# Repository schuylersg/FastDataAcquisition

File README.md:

FastDataAcquisition
===================

A high speed (1 GSPS+) data acquisition circuit. This project is currently in development. All schematics and boards are not finalized.

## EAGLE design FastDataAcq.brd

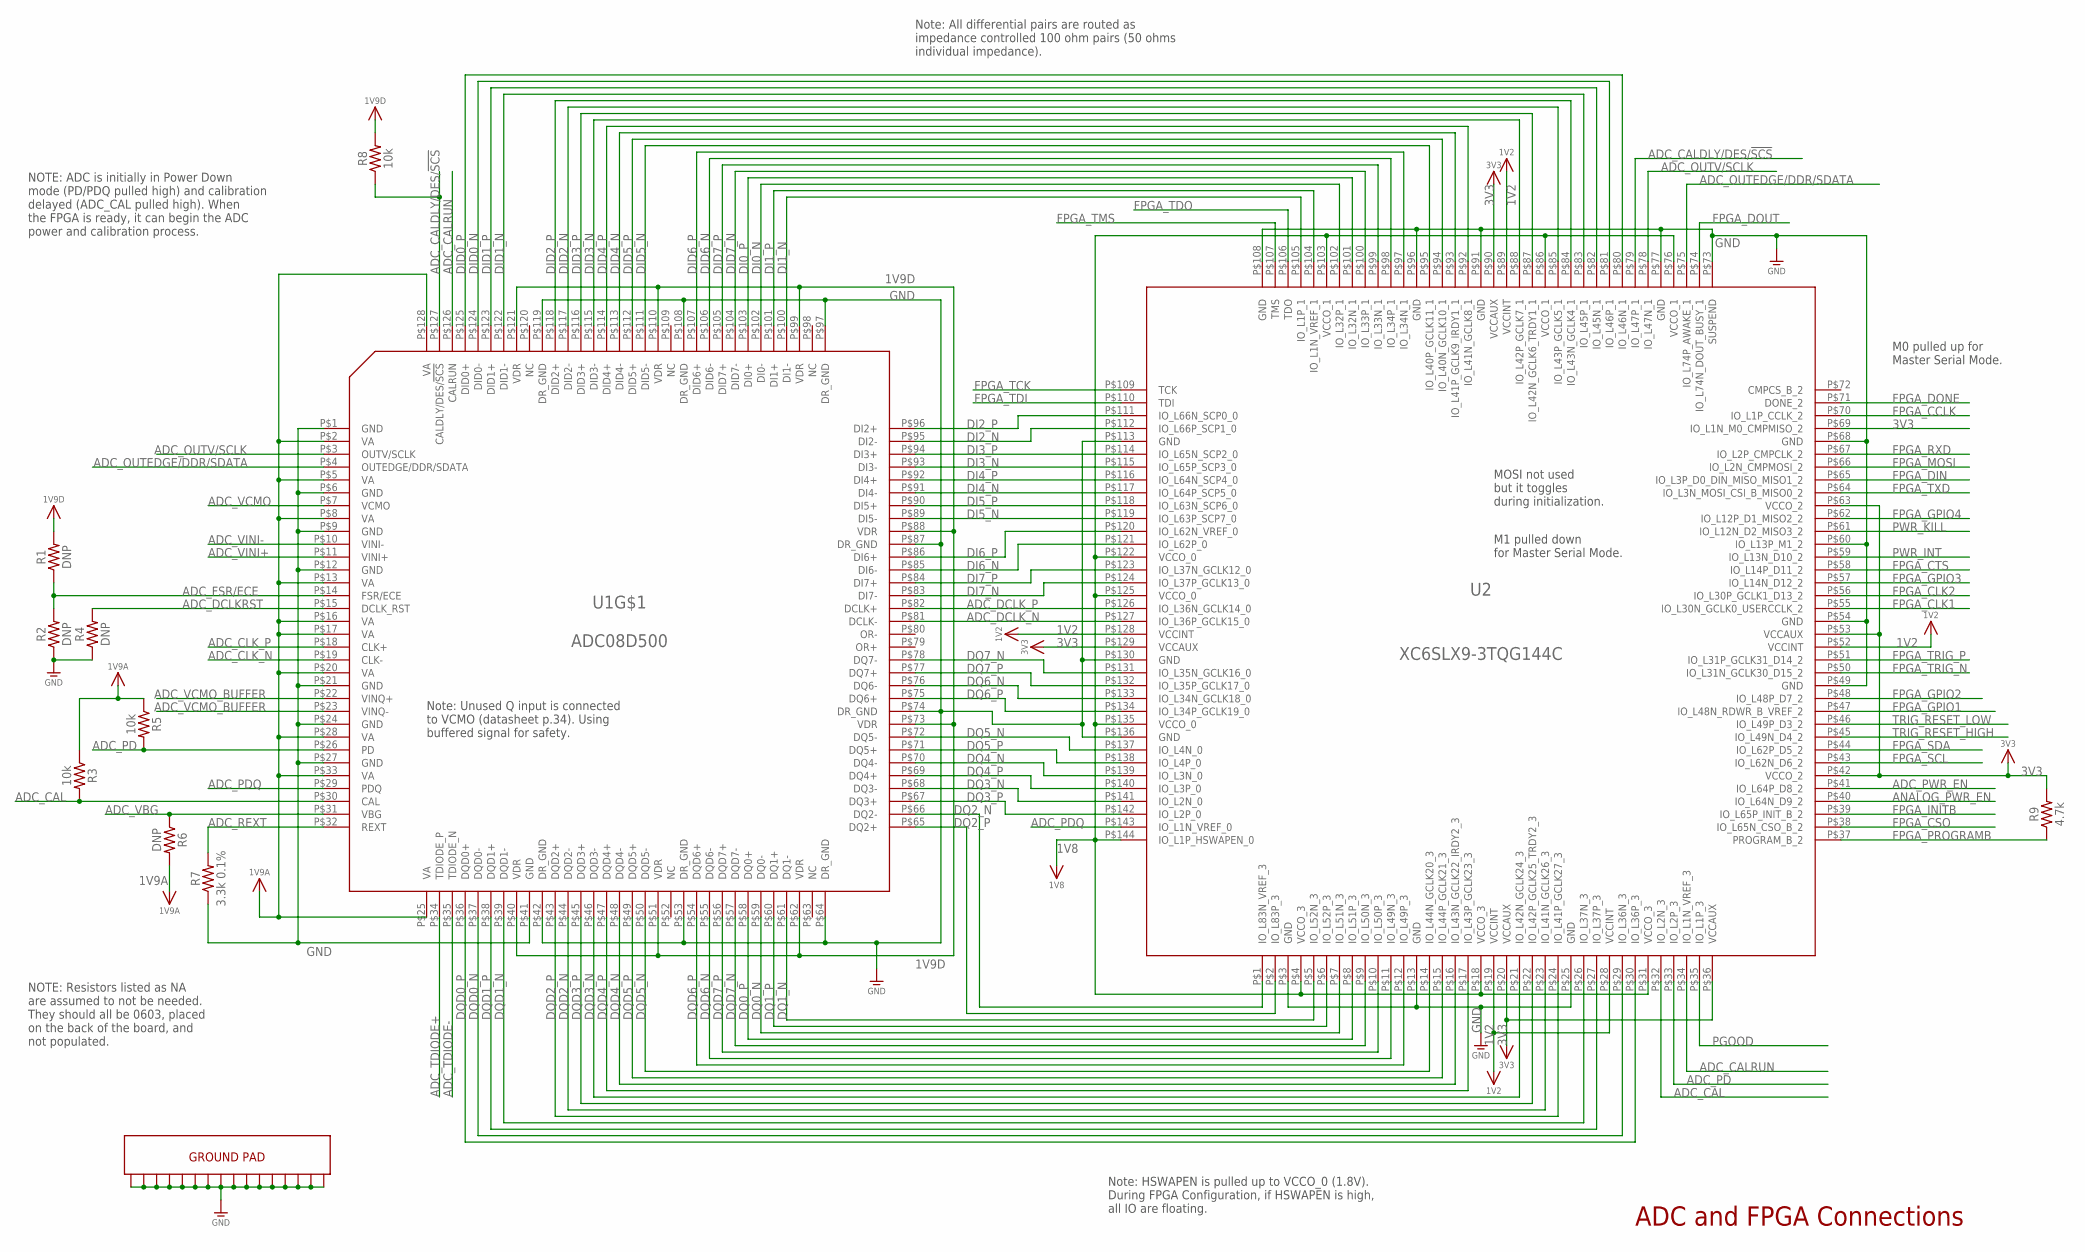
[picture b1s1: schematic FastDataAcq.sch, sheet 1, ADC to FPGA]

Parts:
R1, R2, R4, R6: DNP; R0603
R3, R5, R8: 10k; R0201; MANPARTNUMBER RC0603J103CS
R7: 3.3k 0.1%; R0603; PARTNUMBER P3.3KDBCT-ND
R9: 4.7k; R0201; MANPARTNUMBER ERJ-1GNJ472C
U1: ADC08D500; 128HLQFP; PARTNUMBER ADC08D500CIYB/NOPB-ND
U2: XC6SLX9-3TQG144C; TQG144

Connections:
1V2: U2.P$19 (VCCINT), U2.P$28 (VCCINT), U2.P$52 (VCCINT), U2.P$89 (VCCINT), U2.P$128 (VCCINT); also elsewhere on the board
1V8: U2.P$4 (VCCO_3), U2.P$18 (VCCO_3), U2.P$31 (VCCO_3), U2.P$76 (VCCO_1), U2.P$86 (VCCO_1), U2.P$103 (VCCO_1), U2.P$122 (VCCO_0), U2.P$125 (VCCO_0), U2.P$135 (VCCO_0), U2.P$144 (IO_L1P_HSWAPEN_0); also elsewhere on the board
1V9A: R3.1, R5.1, R6.2, U1.P$2 (VA), U1.P$5 (VA), U1.P$8 (VA), U1.P$13 (VA), U1.P$16 (VA), U1.P$17 (VA), U1.P$20 (VA), U1.P$25 (VA), U1.P$28 (VA), U1.P$33 (VA), U1.P$128 (VA); also elsewhere on the board
1V9D: R1.2, R8.2, U1.P$40 (VDR), U1.P$51 (VDR), U1.P$62 (VDR), U1.P$73 (VDR), U1.P$88 (VDR), U1.P$99 (VDR), U1.P$110 (VDR), U1.P$121 (VDR); also elsewhere on the board
3V3: R9.2, U2.P$20 (VCCAUX), U2.P$36 (VCCAUX), U2.P$42 (VCCO_2), U2.P$53 (VCCAUX), U2.P$63 (VCCO_2), U2.P$69 (IO_L1N_M0_CMPMISO_2), U2.P$90 (VCCAUX), U2.P$129 (VCCAUX); also elsewhere on the board
ADC_CAL: R3.2, U1.P$30 (CAL), U2.P$32 (IO_L2N_3)
ADC_CALDLY/DES/!SCS: R8.1, U1.P$127 (CALDLY/DES/!SCS), U2.P$79 (IO_L47P_1)
ADC_CALRUN: U1.P$126 (CALRUN), U2.P$34 (IO_L1N_VREF_3)
ADC_CLK_N: U1.P$19 (CLK-); also elsewhere on the board
ADC_CLK_P: U1.P$18 (CLK+); also elsewhere on the board
ADC_DCLKRST: R4.2, U1.P$15 (DCLK_RST)
ADC_DCLK_N: U1.P$81 (DCLK-), U2.P$127 (IO_L36P_GCLK15_0)
ADC_DCLK_P: U1.P$82 (DCLK+), U2.P$126 (IO_L36N_GCLK14_0)
ADC_FSR/ECE: R1.1, R2.2, U1.P$14 (FSR/ECE)
ADC_OUTEDGE/DDR/SDATA: U1.P$4 (OUTEDGE/DDR/SDATA), U2.P$75 (IO_L74P_AWAKE_1)
ADC_OUTV/SCLK: U1.P$3 (OUTV/SCLK), U2.P$78 (IO_L47N_1)
ADC_PD: R5.2, U1.P$26 (PD), U2.P$33 (IO_L2P_3)
ADC_PDQ: U1.P$29 (PDQ), U2.P$143 (IO_L1N_VREF_0)
ADC_PWR_EN: U2.P$41 (IO_L64P_D8_2); also elsewhere on the board
ADC_REXT: R7.2, U1.P$32 (REXT)
ADC_TDIODE+: U1.P$34 (TDIODE_P); also elsewhere on the board
ADC_TDIODE-: U1.P$35 (TDIODE_N); also elsewhere on the board
ADC_VBG: R6.1, U1.P$31 (VBG)
ADC_VCMO: U1.P$7 (VCMO); also elsewhere on the board
ADC_VCMO_BUFFER: U1.P$22 (VINQ+), U1.P$23 (VINQ-); also elsewhere on the board
ADC_VINI+: U1.P$11 (VINI+); also elsewhere on the board
ADC_VINI-: U1.P$10 (VINI-); also elsewhere on the board
ANALOG_PWR_EN: U2.P$40 (IO_L64N_D9_2); also elsewhere on the board
DI0_N: U1.P$102 (DI0-), U2.P$102 (IO_L32P_1)
DI0_P: U1.P$103 (DI0+), U2.P$101 (IO_L32N_1)
DI1_N: U1.P$100 (DI1-), U2.P$105 (IO_L1P_1)
DI1_P: U1.P$101 (DI1+), U2.P$104 (IO_L1N_VREF_1)
DI2_N: U1.P$95 (DI2-), U2.P$112 (IO_L66P_SCP1_0)
DI2_P: U1.P$96 (DI2+), U2.P$111 (IO_L66N_SCP0_0)
DI3_N: U1.P$93 (DI3-), U2.P$115 (IO_L65P_SCP3_0)
DI3_P: U1.P$94 (DI3+), U2.P$114 (IO_L65N_SCP2_0)
DI4_N: U1.P$91 (DI4-), U2.P$117 (IO_L64P_SCP5_0)
DI4_P: U1.P$92 (DI4+), U2.P$116 (IO_L64N_SCP4_0)
DI5_N: U1.P$89 (DI5-), U2.P$119 (IO_L63P_SCP7_0)
DI5_P: U1.P$90 (DI5+), U2.P$118 (IO_L63N_SCP6_0)
DI6_N: U1.P$85 (DI6-), U2.P$121 (IO_L62P_0)
DI6_P: U1.P$86 (DI6+), U2.P$120 (IO_L62N_VREF_0)
DI7_N: U1.P$83 (DI7-), U2.P$124 (IO_L37P_GCLK13_0)
DI7_P: U1.P$84 (DI7+), U2.P$123 (IO_L37N_GCLK12_0)
DID0_N: U1.P$124 (DID0-), U2.P$81 (IO_L46P_1)
DID0_P: U1.P$125 (DID0+), U2.P$80 (IO_L46N_1)
DID1_N: U1.P$122 (DID1-), U2.P$83 (IO_L45P_1)
DID1_P: U1.P$123 (DID1+), U2.P$82 (IO_L45N_1)
DID2_N: U1.P$117 (DID2-), U2.P$85 (IO_L43P_GCLK5_1)
DID2_P: U1.P$118 (DID2+), U2.P$84 (IO_L43N_GCLK4_1)
DID3_N: U1.P$115 (DID3-), U2.P$88 (IO_L42P_GCLK7_1)
DID3_P: U1.P$116 (DID3+), U2.P$87 (IO_L42N_GCLK6_TRDY1_1)
DID4_N: U1.P$113 (DID4-), U2.P$93 (IO_L41P_GCLK9_IRDY1_1)
DID4_P: U1.P$114 (DID4+), U2.P$92 (IO_L41N_GCLK8_1)
DID5_N: U1.P$111 (DID5-), U2.P$95 (IO_L40P_GCLK11_1)
DID5_P: U1.P$112 (DID5+), U2.P$94 (IO_L40N_GCLK10_1)
DID6_N: U1.P$106 (DID6-), U2.P$98 (IO_L34P_1)
DID6_P: U1.P$107 (DID6+), U2.P$97 (IO_L34N_1)
DID7_N: U1.P$104 (DID7-), U2.P$100 (IO_L33P_1)
DID7_P: U1.P$105 (DID7+), U2.P$99 (IO_L33N_1)
DQ0_N: U1.P$59 (DQ0-), U2.P$7 (IO_L51N_3)
DQ0_P: U1.P$58 (DQ0+), U2.P$8 (IO_L51P_3)
DQ1_N: U1.P$61 (DQ1-), U2.P$5 (IO_L52N_3)
DQ1_P: U1.P$60 (DQ1+), U2.P$6 (IO_L52P_3)
DQ2_N: U1.P$66 (DQ2-), U2.P$1 (IO_L83N_VREF_3)
DQ2_P: U1.P$65 (DQ2+), U2.P$2 (IO_L83P_3)
DQ3_N: U1.P$68 (DQ3-), U2.P$141 (IO_L2N_0)
DQ3_P: U1.P$67 (DQ3+), U2.P$142 (IO_L2P_0)
DQ4_N: U1.P$70 (DQ4-), U2.P$139 (IO_L3N_0)
DQ4_P: U1.P$69 (DQ4+), U2.P$140 (IO_L3P_0)
DQ5_N: U1.P$72 (DQ5-), U2.P$137 (IO_L4N_0)
DQ5_P: U1.P$71 (DQ5+), U2.P$138 (IO_L4P_0)
DQ6_N: U1.P$76 (DQ6-), U2.P$133 (IO_L34N_GCLK18_0)
DQ6_P: U1.P$75 (DQ6+), U2.P$134 (IO_L34P_GCLK19_0)
DQ7_N: U1.P$78 (DQ7-), U2.P$131 (IO_L35N_GCLK16_0)
DQ7_P: U1.P$77 (DQ7+), U2.P$132 (IO_L35P_GCLK17_0)
DQD0_N: U1.P$37 (DQD0-), U2.P$29 (IO_L36N_3)
DQD0_P: U1.P$36 (DQD0+), U2.P$30 (IO_L36P_3)
DQD1_N: U1.P$39 (DQD1-), U2.P$26 (IO_L37N_3)
DQD1_P: U1.P$38 (DQD1+), U2.P$27 (IO_L37P_3)
DQD2_N: U1.P$44 (DQD2-), U2.P$23 (IO_L41N_GCLK26_3)
DQD2_P: U1.P$43 (DQD2+), U2.P$24 (IO_L41P_GCLK27_3)
DQD3_N: U1.P$46 (DQD3-), U2.P$21 (IO_L42N_GCLK24_3)
DQD3_P: U1.P$45 (DQD3+), U2.P$22 (IO_L42P_GCLK25_TRDY2_3)
DQD4_N: U1.P$48 (DQD4-), U2.P$16 (IO_L43N_GCLK22_IRDY2_3)
DQD4_P: U1.P$47 (DQD4+), U2.P$17 (IO_L43P_GCLK23_3)
DQD5_N: U1.P$50 (DQD5-), U2.P$14 (IO_L44N_GCLK20_3)
DQD5_P: U1.P$49 (DQD5+), U2.P$15 (IO_L44P_GCLK21_3)
DQD6_N: U1.P$55 (DQD6-), U2.P$11 (IO_L49N_3)
DQD6_P: U1.P$54 (DQD6+), U2.P$12 (IO_L49P_3)
DQD7_N: U1.P$57 (DQD7-), U2.P$9 (IO_L50N_3)
DQD7_P: U1.P$56 (DQD7+), U2.P$10 (IO_L50P_3)
FPGA_CCLK: U2.P$70 (IO_L1P_CCLK_2); also elsewhere on the board
FPGA_CLK1: U2.P$55 (IO_L30N_GCLK0_USERCCLK_2); also elsewhere on the board
FPGA_CLK2: U2.P$56 (IO_L30P_GCLK1_D13_2); also elsewhere on the board
FPGA_CSO: U2.P$38 (IO_L65N_CSO_B_2)
FPGA_CTS: U2.P$58 (IO_L14P_D11_2); also elsewhere on the board
FPGA_DIN: U2.P$65 (IO_L3P_D0_DIN_MISO_MISO1_2); also elsewhere on the board
FPGA_DONE: U2.P$71 (DONE_2); also elsewhere on the board
FPGA_DOUT: U2.P$74 (IO_L74N_DOUT_BUSY_1)
FPGA_GPIO1: U2.P$47 (IO_L48N_RDWR_B_VREF_2); also elsewhere on the board
FPGA_GPIO2: U2.P$48 (IO_L48P_D7_2); also elsewhere on the board
FPGA_GPIO3: U2.P$57 (IO_L14N_D12_2); also elsewhere on the board
FPGA_GPIO4: U2.P$62 (IO_L12P_D1_MISO2_2); also elsewhere on the board
FPGA_INITB: U2.P$39 (IO_L65P_INIT_B_2); also elsewhere on the board
FPGA_MOSI: U2.P$66 (IO_L2N_CMPMOSI_2)
FPGA_PROGRAMB: R9.1, U2.P$37 (PROGRAM_B_2); also elsewhere on the board
FPGA_RXD: U2.P$67 (IO_L2P_CMPCLK_2); also elsewhere on the board
FPGA_SCL: U2.P$43 (IO_L62N_D6_2); also elsewhere on the board
FPGA_SDA: U2.P$44 (IO_L62P_D5_2); also elsewhere on the board
FPGA_TCK: U2.P$109 (TCK); also elsewhere on the board
FPGA_TDI: U2.P$110 (TDI); also elsewhere on the board
FPGA_TDO: U2.P$106 (TDO); also elsewhere on the board
FPGA_TMS: U2.P$107 (TMS); also elsewhere on the board
FPGA_TRIG_N: U2.P$50 (IO_L31N_GCLK30_D15_2); also elsewhere on the board
FPGA_TRIG_P: U2.P$51 (IO_L31P_GCLK31_D14_2); also elsewhere on the board
FPGA_TXD: U2.P$64 (IO_L3N_MOSI_CSI_B_MISO0_2); also elsewhere on the board
GND: R2.1, R4.1, R7.1, U1.P$1 (GND), U1.P$6 (GND), U1.P$9 (GND), U1.P$12 (GND), U1.P$21 (GND), U1.P$24 (GND), U1.P$27 (GND), U1.P$41 (GND), U1.P$42 (DR_GND), U1.P$53 (DR_GND), U1.P$64 (DR_GND), U1.P$74 (DR_GND), U1.P$87 (DR_GND), U1.P$97 (DR_GND), U1.P$108 (DR_GND), U1.P$119 (DR_GND), U1.P$129 (GND), U1.P$130 (GND), U1.P$131 (GND), U1.P$132 (GND), U1.P$133 (GND), U1.P$134 (GND), U1.P$135 (GND), U1.P$136 (GND), U1.P$137 (GND), U1.P$138 (GND), U1.P$139 (GND), U1.P$140 (GND), U1.P$141 (GND), U1.P$142 (GND), U1.P$143 (GND), U1.P$144 (GND), U2.P$3 (GND), U2.P$13 (GND), U2.P$25 (GND), U2.P$49 (GND), U2.P$54 (GND), U2.P$60 (IO_L13P_M1_2), U2.P$68 (GND), U2.P$73 (SUSPEND), U2.P$77 (GND), U2.P$91 (GND), U2.P$96 (GND), U2.P$108 (GND), U2.P$113 (GND), U2.P$130 (GND), U2.P$136 (GND); also elsewhere on the board
PGOOD: U2.P$35 (IO_L1P_3); also elsewhere on the board
PWR_INT: U2.P$59 (IO_L13N_D10_2); also elsewhere on the board
PWR_KILL: U2.P$61 (IO_L12N_D2_MISO3_2); also elsewhere on the board
TRIG_RESET_HIGH: U2.P$45 (IO_L49N_D4_2); also elsewhere on the board
TRIG_RESET_LOW: U2.P$46 (IO_L49P_D3_2); also elsewhere on the board

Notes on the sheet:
ADC and FPGA Connections
Note: Unused Q input is connected to VCMO (datasheet p.34). Using buffered signal for safety.
MOSI not used but it toggles during initialization.
M0 pulled up for Master Serial Mode.
M1 pulled down for Master Serial Mode.
Note: HSWAPEN is pulled up to VCCO_0 (1.8V). During FPGA Configuration, if HSWAPEN is high, all IO are floating.
NOTE: Resistors listed as NA are assumed to not be needed. They should all be 0603, placed on the back of the board, and not populated.
NOTE: ADC is initially in Power Down mode (PD/PDQ pulled high) and calibration delayed (ADC_CAL pulled high). When the FPGA is ready, it can begin the ADC power and calibration process.
Note: All differential pairs are routed as impedance controlled 100 ohm pairs (50 ohms individual impedance).

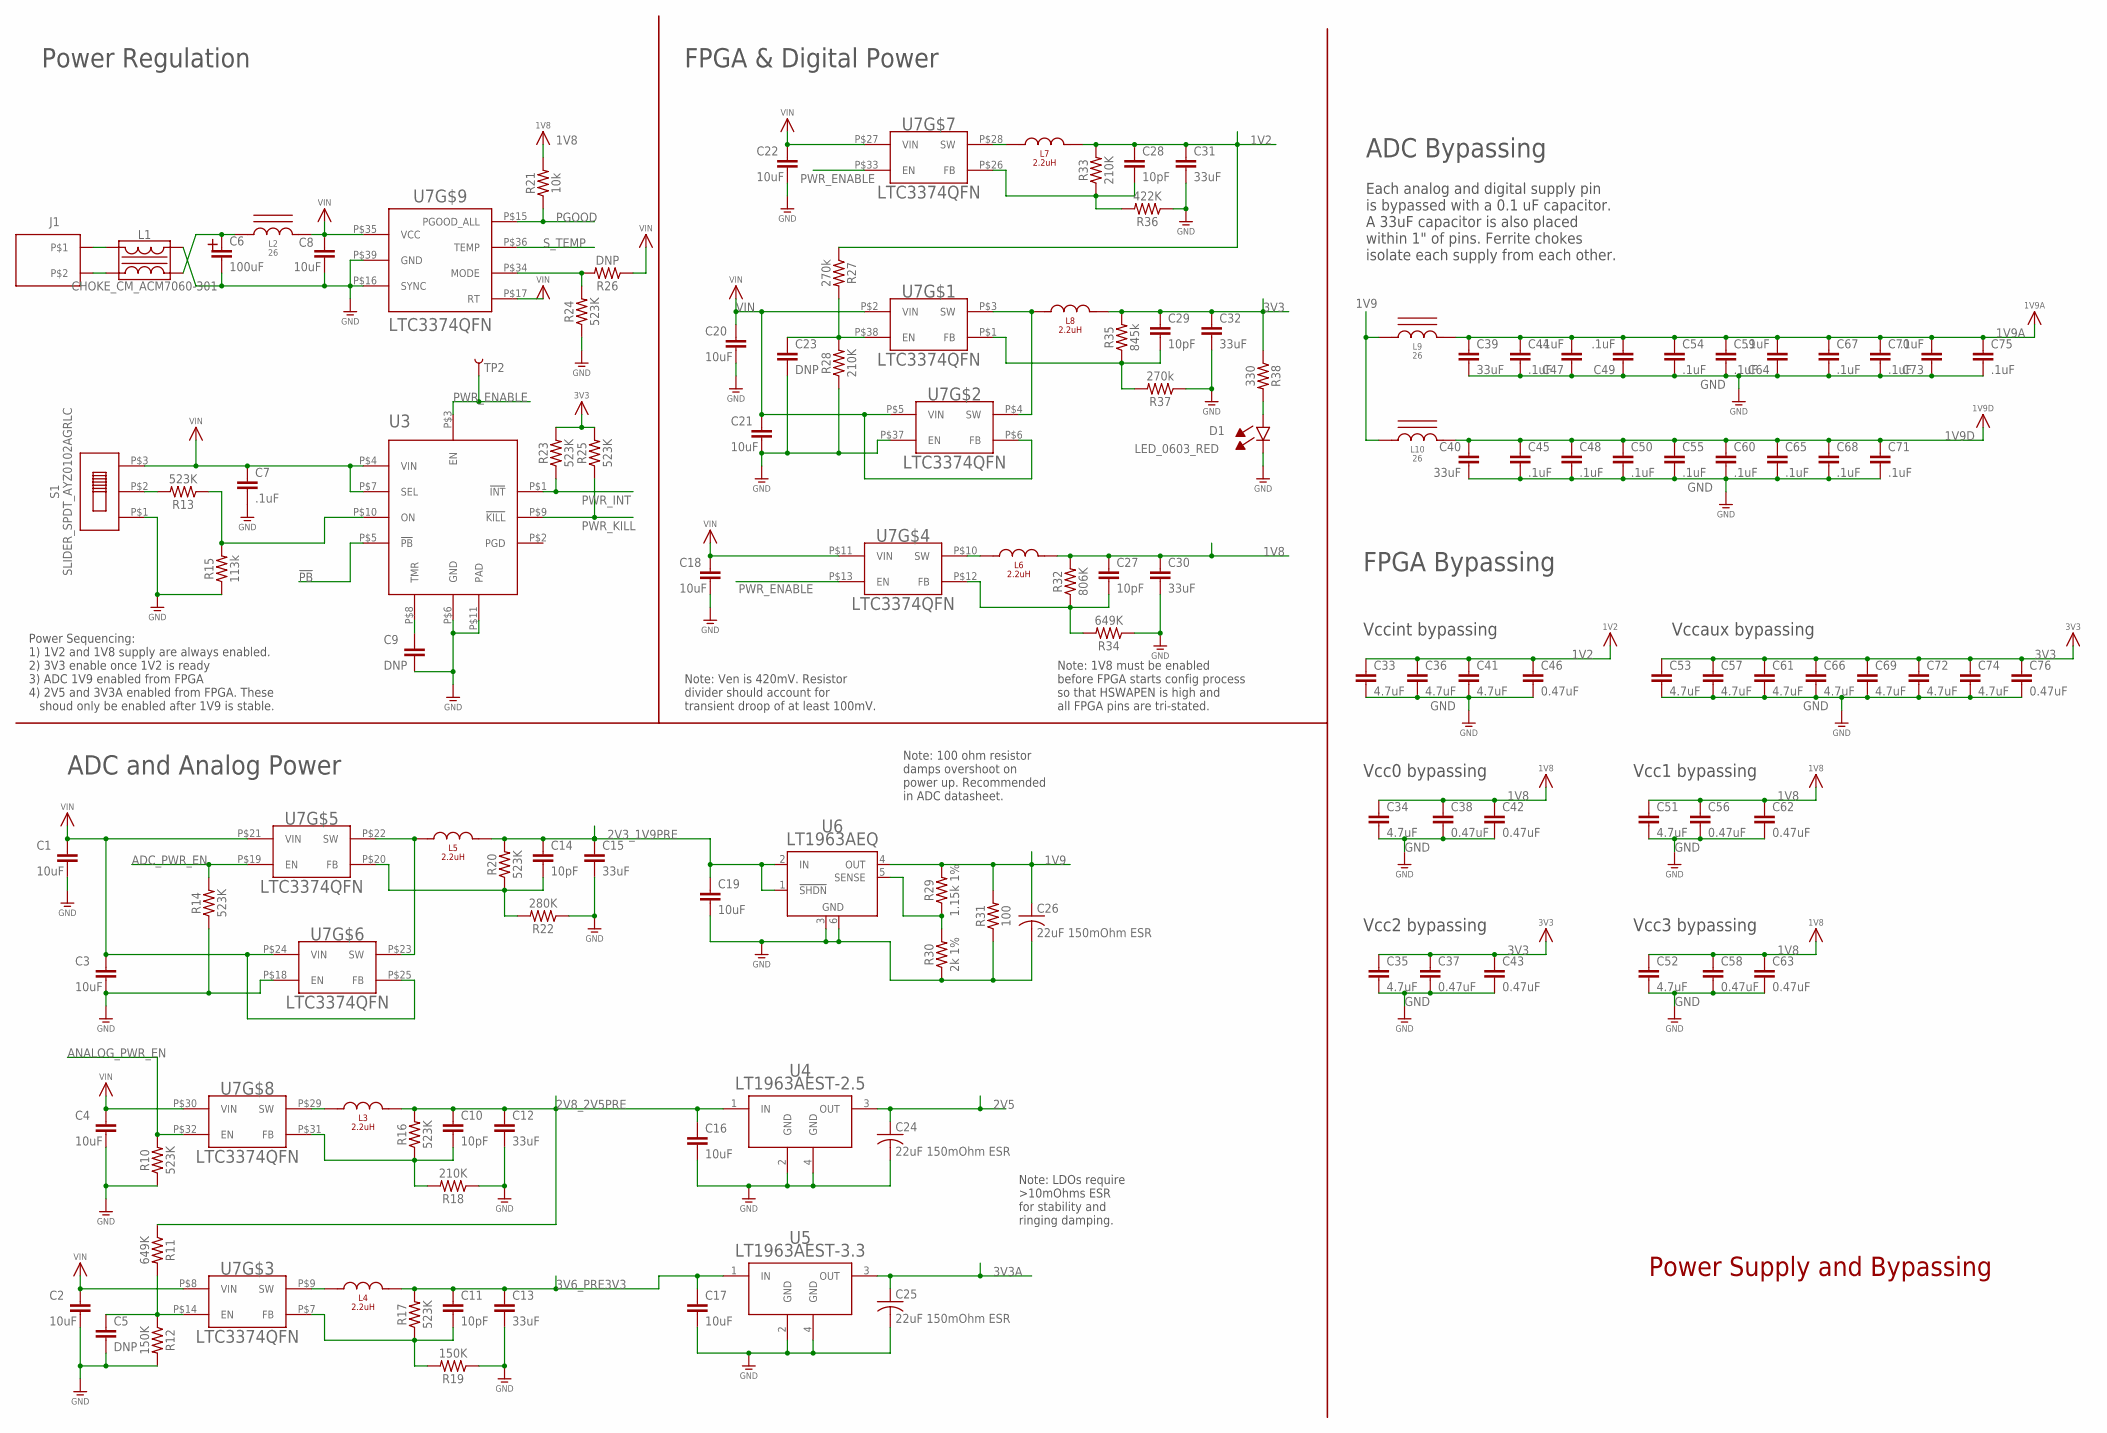
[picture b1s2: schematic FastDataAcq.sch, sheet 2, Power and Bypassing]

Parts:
C1, C2, C3, C4, C8, C16, C17, C18, C19, C20, C21, C22: 10uF; C0603; PARTNUMBER 445-4112-1-ND
C5, C9, C23: DNP; C0603
C6: 100uF; 2917_MURATA_CAP; MANPARTNUMBER ECASD91B107M012K00
C7, C44, C45, C47, C48, C49, C50, C54, C55, C59, C60, C64, C65, C67, C68, C70, C71, C73, C75: .1uF; 0204REVERSE; PARTNUMBER 587-2152-1-ND
C10, C11, C14, C27, C28, C29: 10pF; C0201; PARTNUMBER 445-1769-1-ND
C12, C13, C15, C30, C31, C32, C39, C40: 33uF; 0805; PARTNUMBER 445-8238-1-ND
C24, C25, C26: 22uF 150mOhm ESR; C0805; PARTNUMBER P16231CT-ND
C33, C34, C35, C36, C41, C51, C52, C53, C57, C61, C66, C69, C72, C74: 4.7uF; 0402_C; MANPARTNUMBER CL05A475MQ5NRNC
C37, C38, C42, C43, C46, C56, C58, C62, C63, C76: 0.47uF; 0204REVERSE; PARTNUMBER 1276-1779-1-ND
D1: LED_0603_RED; 0603_LED; PARTNUMBER LNJ237W82RACT-ND
J1: MICRO-FIT_3.0_2POS_RA_SMD; MICRO-FIT_3.02POS_RA_SMD
L1: CHOKE_CM_ACM7060-301; ACM7060_CHOKE
L2, L9, L10: 26; MURATA_BLM18
L3, L4, L6, L7: 2.2uH; 3.0X3.6_VISHAY; PARTNUMBER 541-1322-1-ND
L5, L8: 2.2uH; 5.18X5.49_VISHAY; PARTNUMBER 541-1220-1-ND
R10, R13, R14, R16, R17, R20, R23, R24, R25: 523K; R0201; PARTNUMBER P523KABCT-ND
R11, R34: 649K; R0201; PARTNUMBER P649KABCT-ND
R12, R19: 150K; R0201; PARTNUMBER 1276-3719-1-ND
R15: 113k; R0201; PARTNUMBER P113KABCT-ND
R18, R28, R33: 210K; R0201; PARTNUMBER P210KABCT-ND
R21: 10k; R0201; MANPARTNUMBER RC0603J103CS
R22: 280K; R0201; PARTNUMBER P280KABCT-ND
R26: DNP; R0603
R27, R37: 270k; R0201; PARTNUMBER P270KABCT-ND
R29: 1.15k 1%; R0603; MANPARTNUMBER RC1608F1151CS
R30: 2k 1%; R0603; MANPARTNUMBER RC1608F202CS
R31: 100; R0603; MANPARTNUMBER RC1608J101CS
R32: 806K; R0201; PARTNUMBER P806KABCT-ND
R35: 845k; R0201; PARTNUMBER P845KABCT-ND
R36: 422K; R0201; PARTNUMBER P422KABCT-ND
R38: 330; R0201; MANPARTNUMBER RC0603J331CS
S1: SLIDER_SPDT_AYZ0102AGRLC; AYZ0102AGRLC
TP2: TEST-POINT3; PAD.03X.03
U3: LTC2955-1; 10-DFN
U4: LT1963AEST-2.5; SOT223
U5: LT1963AEST-3.3; SOT223
U6: LT1963AEQ; Q5-DD; MANPARTNUMBER LT1963AEQ#PBF
U7: LTC3374QFN; 38-QFN_(5X7)

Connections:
1V2: C28.1, C31.1, C33.P$1 (1), C36.P$1 (1), C41.P$1 (1), C46.P$1 (1), L7.P$2, R27.1, R33.2; also elsewhere on the board
1V8: C27.1, C30.1, C34.P$1 (1), C38.P$1 (1), C42.P$1 (1), C51.P$1 (1), C52.P$1 (1), C56.P$1 (1), C58.P$1 (1), C62.P$1 (1), C63.P$1 (1), L6.P$2, R21.2, R32.2; also elsewhere on the board
1V9: C26.1, L9.P$1, L10.P$1, R29.2, R31.2, U6.4 (OUT)
1V9A: C39.1, C44.P$1 (1), C47.P$2 (2), C49.P$2 (2), C54.P$1 (1), C59.P$1 (1), C64.P$2 (2), C67.P$1 (1), C70.P$1 (1), C73.P$2 (2), C75.P$1 (1), L9.P$2; also elsewhere on the board
1V9D: C40.1, C45.P$1 (1), C48.P$1 (1), C50.P$1 (1), C55.P$1 (1), C60.P$1 (1), C65.P$1 (1), C68.P$1 (1), C71.P$1 (1), L10.P$2; also elsewhere on the board
2V3_1V9PRE: C14.1, C15.1, C19.1, L5.P$2, R20.2, U6.1 (!SHDN), U6.2 (IN)
2V5: C24.1, U4.3 (OUT); also elsewhere on the board
2V8_2V5PRE: C10.1, C12.1, C16.1, L3.P$2, R11.1, R16.2, U4.1 (IN)
3V3: C29.1, C32.1, C35.P$1 (1), C37.P$1 (1), C43.P$1 (1), C53.P$1 (1), C57.P$1 (1), C61.P$1 (1), C66.P$1 (1), C69.P$1 (1), C72.P$1 (1), C74.P$1 (1), C76.P$1 (1), L8.P$2, R23.2, R25.2, R35.2, R38.1; also elsewhere on the board
3V3A: C25.1, U5.3 (OUT); also elsewhere on the board
3V6_PRE3V3: C11.1, C13.1, C17.1, L4.P$2, R17.2, U5.1 (IN)
!PB: U3.P$5 (!PB); also elsewhere on the board
ADC_PWR_EN: R14.2, U7.P$19 (EN); also elsewhere on the board
ANALOG_PWR_EN: R10.2, U7.P$32 (EN); also elsewhere on the board
GND: C1.2, C2.2, C3.2, C4.2, C5.2, C6.P$2 (NEG), C7.P$2 (2), C8.2, C9.2, C12.2, C13.2, C15.2, C16.2, C17.2, C18.2, C19.2, C20.2, C21.2, C22.2, C23.2, C24.2, C25.2, C26.2, C30.2, C31.2, C32.2, C33.P$2 (2), C34.P$2 (2), C35.P$2 (2), C36.P$2 (2), C37.P$2 (2), C38.P$2 (2), C39.2, C40.2, C41.P$2 (2), C42.P$2 (2), C43.P$2 (2), C44.P$2 (2), C45.P$2 (2), C46.P$2 (2), C47.P$1 (1), C48.P$2 (2), C49.P$1 (1), C50.P$2 (2), C51.P$2 (2), C52.P$2 (2), C53.P$2 (2), C54.P$2 (2), C55.P$2 (2), C56.P$2 (2), C57.P$2 (2), C58.P$2 (2), C59.P$2 (2), C60.P$2 (2), C61.P$2 (2), C62.P$2 (2), C63.P$2 (2), C64.P$1 (1), C65.P$2 (2), C66.P$2 (2), C67.P$2 (2), C68.P$2 (2), C69.P$2 (2), C70.P$2 (2), C71.P$2 (2), C72.P$2 (2), C73.P$1 (1), C74.P$2 (2), C75.P$2 (2), C76.P$2 (2), D1.CATHODE, L1.P$4, R10.1, R12.2, R14.1, R15.1, R18.1, R19.1, R22.1, R24.1, R28.1, R30.1, R31.1, R34.1, R36.1, R37.1, S1.P$1, U3.P$6 (GND), U3.P$11 (PAD), U4.2 (GND), U4.4 (GND), U5.2 (GND), U5.4 (GND), U6.3 (GND), U6.6 (GND), U7.P$16 (SYNC), U7.P$18 (EN), U7.P$37 (EN), U7.P$39 (GND); also elsewhere on the board
unnamed: D1.ANODE, R38.2
unnamed: R13.2, S1.P$2
unnamed: R13.1, R15.2, U3.P$10 (ON)
unnamed: R29.1, R30.2, U6.5 (SENSE)
unnamed: C9.1, U3.P$8 (TMR)
unnamed: C6.P$1 (POS), L1.P$3, L2.P$1
unnamed: J1.P$1, L1.P$1
unnamed: J1.P$2, L1.P$2
PGOOD: R21.1, U7.P$15 (PGOOD_ALL); also elsewhere on the board
PWR_ENABLE: TP2.P$1, U3.P$3 (EN), U7.P$13 (EN), U7.P$33 (EN)
PWR_INT: R23.1, U3.P$1 (!INT); also elsewhere on the board
PWR_KILL: R25.1, U3.P$9 (!KILL); also elsewhere on the board
S1EN: C23.1, R27.2, R28.2, U7.P$38 (EN)
S1FB: C29.2, R35.1, R37.2, U7.P$1 (FB)
S1SW: L8.P$1, U7.P$3 (SW), U7.P$4 (SW)
S3EN: C5.1, R11.2, R12.1, U7.P$14 (EN)
S3FB: C11.2, R17.1, R19.2, U7.P$7 (FB)
S3SW: L4.P$1, U7.P$9 (SW)
S4FB: C27.2, R32.1, R34.2, U7.P$12 (FB)
S4SW: L6.P$1, U7.P$10 (SW)
S5FB: C14.2, R20.1, R22.2, U7.P$20 (FB)
S5SW: L5.P$1, U7.P$22 (SW), U7.P$23 (SW)
S7FB: C28.2, R33.1, R36.2, U7.P$26 (FB)
S7SW: L7.P$1, U7.P$28 (SW)
S8FB: C10.2, R16.1, R18.2, U7.P$31 (FB)
S8SW: L3.P$1, U7.P$29 (SW)
S_MODE: R24.2, R26.2, U7.P$34 (MODE)
S_TEMP: U7.P$36 (TEMP); also elsewhere on the board
VIN: C1.1, C2.1, C3.1, C4.1, C7.P$1 (1), C8.1, C18.1, C20.1, C21.1, C22.1, L2.P$2, R26.1, S1.P$3, U3.P$4 (VIN), U3.P$7 (SEL), U7.P$2 (VIN), U7.P$5 (VIN), U7.P$6 (FB), U7.P$8 (VIN), U7.P$11 (VIN), U7.P$17 (RT), U7.P$21 (VIN), U7.P$24 (VIN), U7.P$25 (FB), U7.P$27 (VIN), U7.P$30 (VIN), U7.P$35 (VCC)

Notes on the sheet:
Power Supply and Bypassing
ADC Bypassing
Each analog and digital supply pin is bypassed with a 0.1 uF capacitor. A 33uF capacitor is also placed within 1" of pins. Ferrite chokes isolate each supply from each other.
FPGA Bypassing
Vccint bypassing
Vccaux bypassing
Vcc0 bypassing
Vcc1 bypassing
Vcc2 bypassing
Vcc3 bypassing
Note: Ven is 420mV. Resistor divider should account for transient droop of at least 100mV.
Power Regulation
FPGA & Digital Power
ADC and Analog Power
Note: LDOs require >10mOhms ESR for stability and ringing damping.
Power Sequencing: 1) 1V2 and 1V8 supply are always enabled. 2) 3V3 enable once 1V2 is ready 3) ADC 1V9 enabled from FPGA 4) 2V5 and 3V3A enabled from FPGA. These shoud only be enabled after 1V9 is stable.
Note: 100 ohm resistor damps overshoot on power up. Recommended in ADC datasheet.
Note: 1V8 must be enabled before FPGA starts config process so that HSWAPEN is high and all FPGA pins are tri-stated.

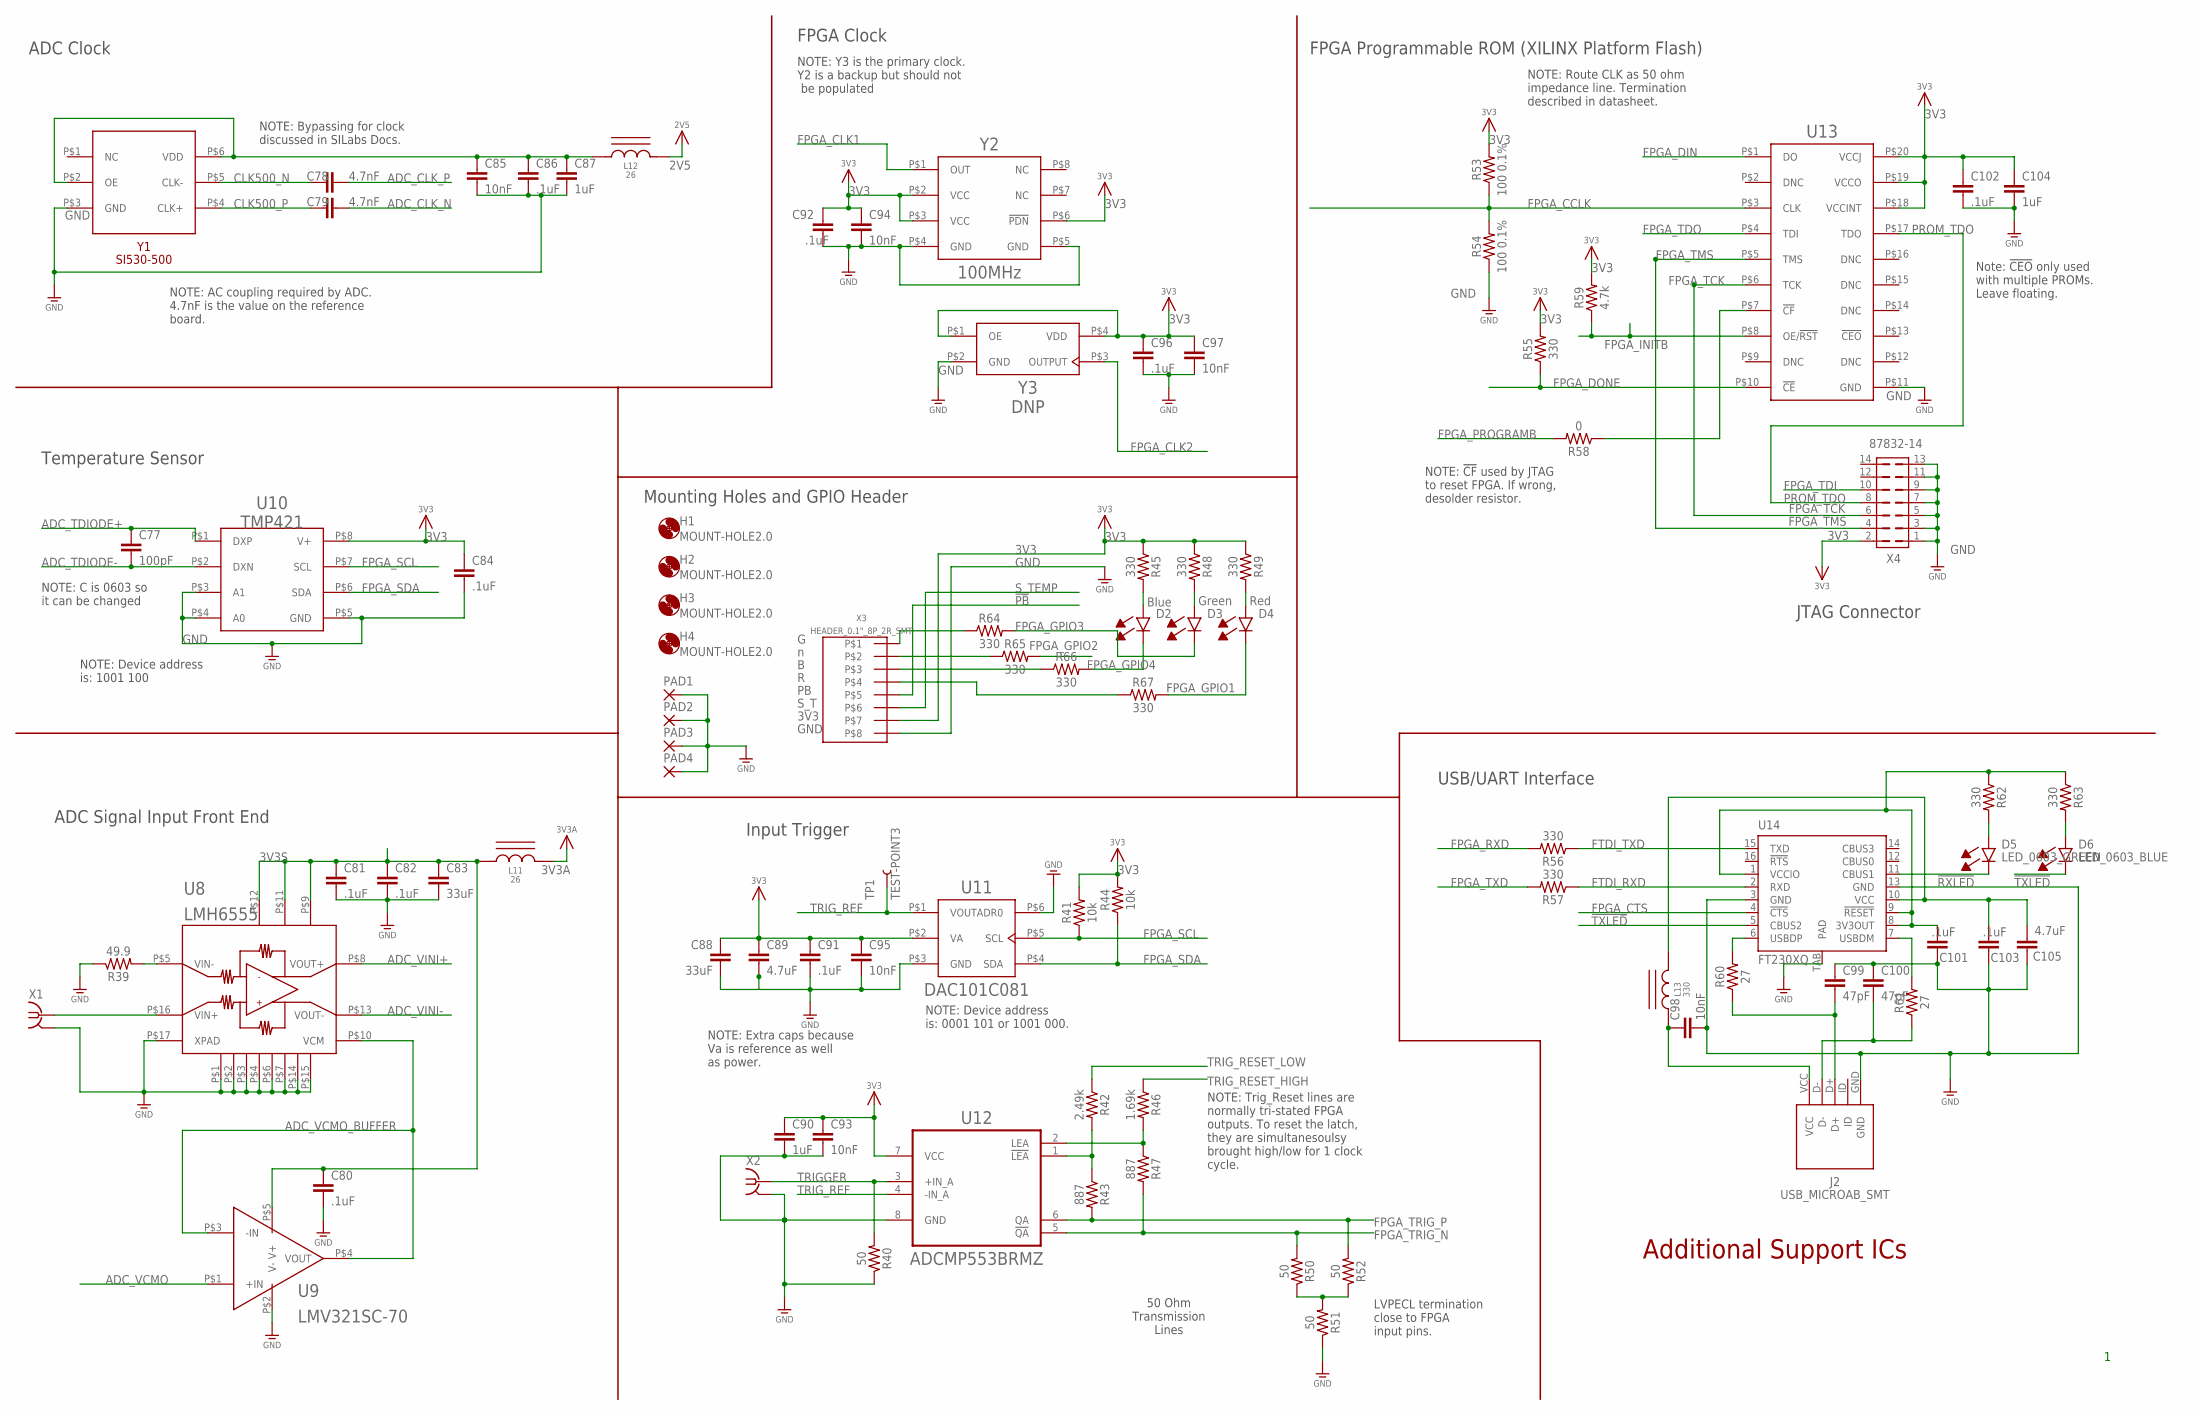
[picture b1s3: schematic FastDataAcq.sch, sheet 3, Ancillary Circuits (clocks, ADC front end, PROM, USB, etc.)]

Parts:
C77: 100pF; C0201; PARTNUMBER 445-4675-1-ND
C78, C79: 4.7nF; C0201; PARTNUMBER 445-13726-1-ND
C80, C81, C82, C84, C86, C91, C92, C96, C101, C102, C103: .1uF; 0204REVERSE; PARTNUMBER 587-2152-1-ND
C83, C88: 33uF; 0805; PARTNUMBER 445-8238-1-ND
C85, C93, C94, C95, C97, C98: 10nF; C0201; PARTNUMBER 445-1793-1-ND
C87, C90, C104: 1uF; 0204REVERSE; PARTNUMBER 445-9091-1-ND
C89, C105: 4.7uF; 0402_C; MANPARTNUMBER CL05A475MQ5NRNC
C99, C100: 47pF; C0201; PARTNUMBER 445-1782-1-ND
D2, D6: LED_0603_BLUE; 0603_LED
D3, D5: LED_0603_GREEN; 0603_LED
D4: LED_0603_RED; 0603_LED; PARTNUMBER LNJ237W82RACT-ND
H1, H2, H3, H4: MOUNT-HOLE2.0; 2.0
J2: USB_MICROAB_SMT; USB_MICROAB_SMT_1
L11, L12: 26; MURATA_BLM18
L13: 330; MURATA_BLM18
PAD1, PAD2, PAD3, PAD4: SMD2; SMD1,27-2,54
R39: 49.9; R0201; MANPARTNUMBER RC0603F49R9C
R40, R50, R51, R52: 50; R0201; MANPARTNUMBER RC0603F49R9C
R41, R44: 10k; R0201; MANPARTNUMBER RC0603J103CS
R42: 2.49k; R0603; PARTNUMBER 1276-4681-1-ND
R43, R47: 887; R0201; MANPARTNUMBER ERJ-1GEF8870C
R45, R48, R49, R55, R56, R57, R62, R63, R64, R65, R66, R67: 330; R0201; MANPARTNUMBER RC0603J331CS
R46: 1.69k; R0603; PARTNUMBER 1276-3491-1-ND
R53, R54: 100 0.1%; R0402; MANPARTNUMBER ERA-3AEB101V
R58: 0; R0603; PARTNUMBER 311-0.0GRCT-ND
R59: 4.7k; R0201; MANPARTNUMBER ERJ-1GNJ472C
R60, R61: 27; R0201; PARTNUMBER 1276-3577-1-ND
TP1: TEST-POINT3; PAD.03X.03
U8: LMH6555; 16WQFN
U9: LMV321SC-70; SC-70
U10: TMP421; SOT23-8
U11: DAC101C081; SOT23-6
U12: ADCMP553BRMZ; SOP65P490X110-8N
U13: XCFXXS04; TSSOP20_XILINX
U14: FT230XQ; QFN16
X1, X2: SMA-142-0701-801/806; J502-ND-142-0701-801/806; MANPARTNUMBER 142-0701-801
X3: HEADER_0.1"_8P_2R_SMT; HEADER_8P_2R_SMT
X4: 87832-14
Y1: SI530-500; SI530
Y2: 100MHz; UMAX8
Y3: DNP; SI500S

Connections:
2V5: L12.P$2; also elsewhere on the board
2V5A: C85.1, C86.P$1 (1), C87.P$1 (1), L12.P$1, Y1.P$2 (OE), Y1.P$6 (VDD)
3V3: C84.P$1 (1), C88.1, C89.P$1 (1), C90.P$1 (1), C91.P$1 (1), C92.P$1 (1), C93.1, C94.1, C95.1, C96.P$1 (1), C97.1, C102.P$1 (1), C104.P$1 (1), R41.2, R44.2, R45.1, R48.1, R49.1, R53.2, R55.2, R59.2, U10.P$8 (V+), U11.P$2 (VA), U12.7 (VCC), U13.P$18 (VCCINT), U13.P$19 (VCCO), U13.P$20 (VCCJ), X3.P$7, X4.2, Y2.P$2 (VCC), Y2.P$3 (VCC), Y2.P$6 (!PDN), Y3.P$1 (OE), Y3.P$4 (VDD); also elsewhere on the board
3V3A: L11.P$2; also elsewhere on the board
3V3OUT: C101.P$2 (2), R62.1, R63.1, U14.1 (VCCIO), U14.8 (3V3OUT), U14.9 (!RESET)
3V3S: C80.P$1 (1), C81.P$1 (1), C82.P$1 (1), C83.1, L11.P$1, U8.P$9 (VCC), U8.P$11 (VCC), U8.P$12 (VCC), U9.P$5 (V+)
5VUSB: C103.P$2 (2), C105.P$2 (2), L13.P$2, U14.10 (VCC)
5VUSB_CON: C98.1, J2.VCC, L13.P$1
!PB: X3.P$5; also elsewhere on the board
!RXLED: D5.CATHODE, U14.11 (CBUS1)
!TXLED: D6.CATHODE, U14.5 (CBUS2)
ADC_CLK_N: C79.2; also elsewhere on the board
ADC_CLK_P: C78.2; also elsewhere on the board
ADC_TDIODE+: C77.1, U10.P$1 (DXP); also elsewhere on the board
ADC_TDIODE-: C77.2, U10.P$2 (DXN); also elsewhere on the board
ADC_VCMO: U9.P$1 (+IN); also elsewhere on the board
ADC_VCMO_BUFFER: U8.P$10 (VCM), U9.P$3 (-IN), U9.P$4 (VOUT); also elsewhere on the board
ADC_VINI+: U8.P$8 (VOUT+); also elsewhere on the board
ADC_VINI-: U8.P$13 (VOUT-); also elsewhere on the board
CLK500_N: C78.1, Y1.P$5 (CLK-)
CLK500_P: C79.1, Y1.P$4 (CLK+)
FPGA_CCLK: R53.1, R54.2, U13.P$3 (CLK); also elsewhere on the board
FPGA_CLK1: Y2.P$1 (OUT); also elsewhere on the board
FPGA_CLK2: Y3.P$3 (OUTPUT); also elsewhere on the board
FPGA_CTS: U14.4 (!CTS); also elsewhere on the board
FPGA_DIN: U13.P$1 (DO); also elsewhere on the board
FPGA_DONE: R55.1, U13.P$10 (!CE); also elsewhere on the board
FPGA_GPIO1: D4.CATHODE, R67.2; also elsewhere on the board
FPGA_GPIO2: R65.2; also elsewhere on the board
FPGA_GPIO3: D3.CATHODE, R64.2; also elsewhere on the board
FPGA_GPIO4: D2.CATHODE, R66.2; also elsewhere on the board
FPGA_INITB: R59.1, U13.P$8 (OE/!RST); also elsewhere on the board
FPGA_PROGRAMB: R58.2; also elsewhere on the board
FPGA_RXD: R56.2; also elsewhere on the board
FPGA_SCL: R41.1, U10.P$7 (SCL), U11.P$5 (SCL); also elsewhere on the board
FPGA_SDA: R44.1, U10.P$6 (SDA), U11.P$4 (SDA); also elsewhere on the board
FPGA_TCK: U13.P$6 (TCK), X4.6; also elsewhere on the board
FPGA_TDI: X4.10; also elsewhere on the board
FPGA_TDO: U13.P$4 (TDI); also elsewhere on the board
FPGA_TMS: U13.P$5 (TMS), X4.4; also elsewhere on the board
FPGA_TRIG_N: R47.2, R50.2, U12.5 (!QA); also elsewhere on the board
FPGA_TRIG_P: R43.2, R52.2, U12.6 (QA); also elsewhere on the board
FPGA_TXD: R57.2; also elsewhere on the board
FTDI_RXD: R57.1, U14.2 (RXD)
FTDI_TXD: R56.1, U14.15 (TXD)
GND: C80.P$2 (2), C81.P$2 (2), C82.P$2 (2), C83.2, C84.P$2 (2), C85.2, C86.P$2 (2), C87.P$2 (2), C88.2, C89.P$2 (2), C90.P$2 (2), C91.P$2 (2), C92.P$2 (2), C93.2, C94.2, C95.2, C96.P$2 (2), C97.2, C98.2, C99.1, C100.1, C101.P$1 (1), C102.P$2 (2), C103.P$1 (1), C104.P$2 (2), C105.P$1 (1), J2.GND, PAD1.1, PAD2.1, PAD3.1, PAD4.1, R39.1, R40.1, R51.1, R54.1, U8.P$1 (GND), U8.P$2 (GND), U8.P$3 (GND), U8.P$4 (GND), U8.P$6 (GND), U8.P$7 (GND), U8.P$14 (GND), U8.P$15 (GND), U8.P$17 (XPAD), U9.P$2 (V-), U10.P$3 (A1), U10.P$4 (A0), U10.P$5 (GND), U11.P$3 (GND), U11.P$6 (ADR0), U12.8 (GND), U13.P$11 (GND), U14.3 (GND), U14.13 (GND), U14.TAB (PAD), X1.G@1 (2), X1.G@2 (2), X1.G@3 (2), X1.G@4 (2), X2.G@1 (2), X2.G@2 (2), X2.G@3 (2), X2.G@4 (2), X3.P$8, X4.1, X4.3, X4.5, X4.7, X4.9, X4.11, X4.13, Y1.P$3 (GND), Y2.P$4 (GND), Y2.P$5 (GND), Y3.P$2 (GND); also elsewhere on the board
unnamed: R39.2, U8.P$5 (VIN-)
unnamed: R60.2, U14.6 (USBDP)
unnamed: C99.2, J2.D+, R60.1
unnamed: C100.2, J2.D-, R61.1
unnamed: R61.2, U14.7 (USBDM)
unnamed: R64.1, X3.P$1
unnamed: D5.ANODE, R62.2
unnamed: R58.1, U13.P$7 (!CF)
unnamed: D6.ANODE, R63.2
unnamed: R42.2, R43.1, U12.1 (!LEA)
unnamed: R50.1, R51.2, R52.1
unnamed: D4.ANODE, R49.2
unnamed: R46.2, R47.1, U12.2 (LEA)
unnamed: D3.ANODE, R48.2
unnamed: D2.ANODE, R45.2
unnamed: R65.1, X3.P$2
unnamed: R66.1, X3.P$3
unnamed: R67.1, X3.P$4
PROM_TDO: U13.P$17 (TDO), X4.8
SIGNAL_IN: U8.P$16 (VIN+), X1.1
S_TEMP: X3.P$6; also elsewhere on the board
TRIGGER: R40.2, U12.3 (+IN_A), X2.1
TRIG_REF: TP1.P$1, U11.P$1 (VOUT), U12.4 (-IN_A)
TRIG_RESET_HIGH: R46.1; also elsewhere on the board
TRIG_RESET_LOW: R42.1; also elsewhere on the board

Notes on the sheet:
NOTE: Bypassing for clock discussed in SILabs Docs.
ADC Clock
NOTE: AC coupling required by ADC. 4.7nF is the value on the reference board.
ADC Signal Input Front End
NOTE: Route CLK as 50 ohm impedance line. Termination described in datasheet.
Note: !CEO! only used with multiple PROMs. Leave floating.
NOTE: !CF! used by JTAG to reset FPGA. If wrong, desolder resistor.
FPGA Programmable ROM (XILINX Platform Flash)
JTAG Connector
USB/UART Interface
FPGA Clock
NOTE: Y3 is the primary clock. Y2 is a backup but should not be populated
NOTE: C is 0603 so it can be changed
Temperature Sensor
Input Trigger
NOTE: Device address is: 1001 100
NOTE: Device address is: 0001 101 or 1001 000.
NOTE: Extra caps because Va is reference as well as power.
50 Ohm Transmission Lines
LVPECL termination close to FPGA input pins.
NOTE: Trig_Reset lines are normally tri-stated FPGA outputs. To reset the latch, they are simultanesoulsy brought high/low for 1 clock cycle.
Additional Support ICs
Mounting Holes and GPIO Header
Blue
Green
Red
S_T
3V3
GND

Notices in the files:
parts and their libraries:
SparkFun-Passives: Licensing: CC v3.0 Share-Alike You are welcome to use this library for commercial purposes.
